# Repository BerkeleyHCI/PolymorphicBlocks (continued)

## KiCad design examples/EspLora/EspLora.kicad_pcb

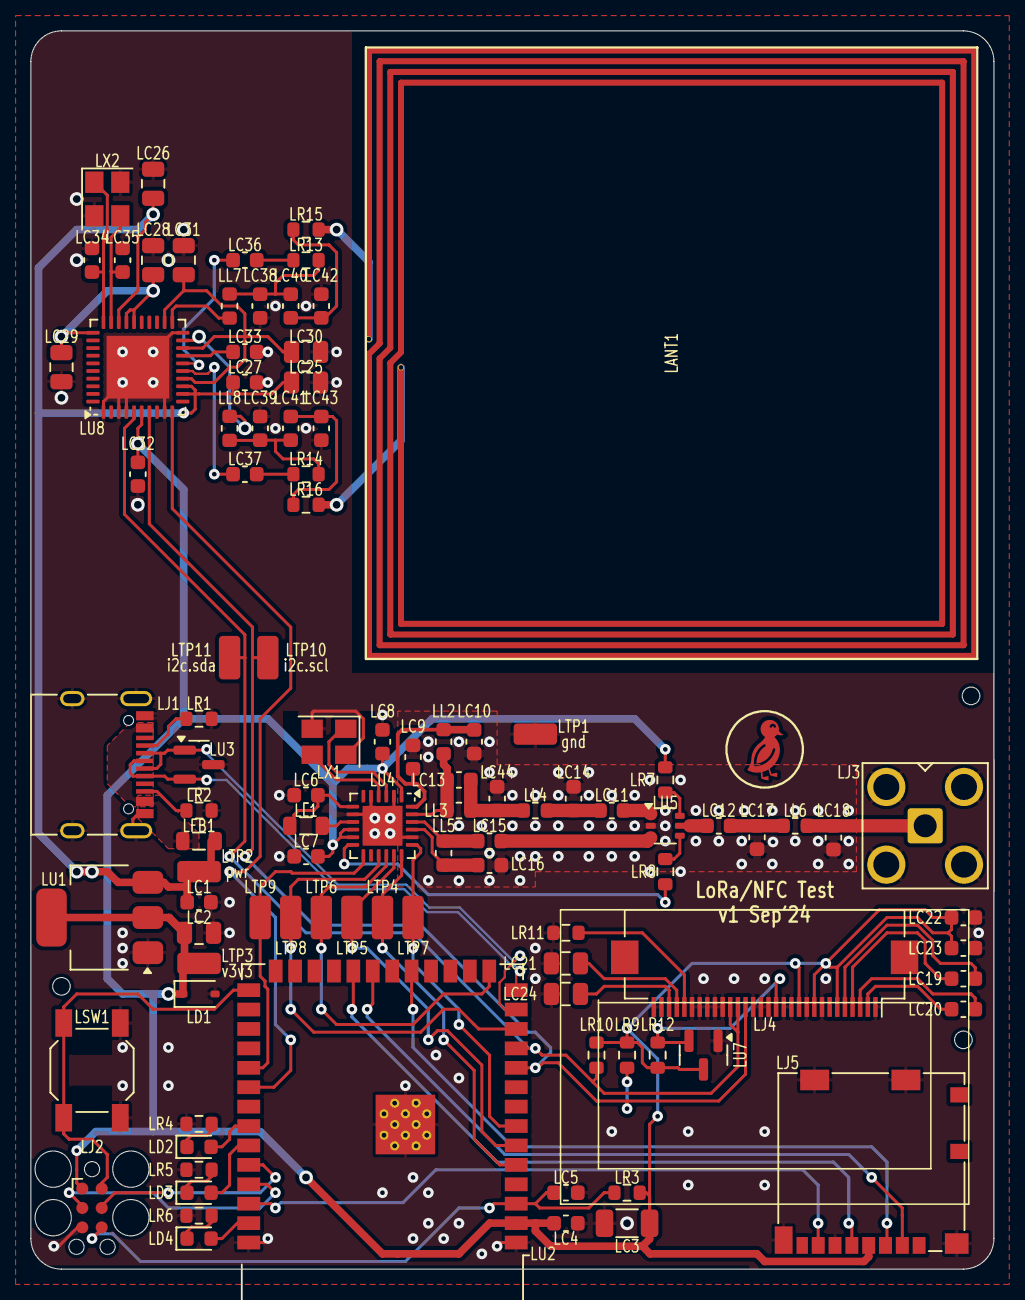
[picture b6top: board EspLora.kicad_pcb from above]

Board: 2 copper layers, 63.0 x 81.0 mm, 105 parts (0 on the bottom side), 74 nets.

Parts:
LANT1: an13219
LC1, LC4, LC7, LC27, LC33: 50V 100nF X7R ±10% 0603 Multilayer Ceramic Capaci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; C_0603_1608Metric
LC2, LC21, LC25, LC26: 25V 4.7uF X5R ±10% 0805 Multilayer Ceramic Capaci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; C_0805_2012Metric
LC3: 25V 22uF X5R ±10% 1206 Multilayer Ceramic Capacit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; C_1206_3216Metric
LC5, LC8, LC19, LC20, LC22, LC23, LC32: 50V 1uF X5R ±10% 0603 Multilayer Ceramic Capacito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; C_0603_1608Metric
LC6: 25V 470nF X7R ±10% 0603 Multilayer Ceramic Capaci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; C_0603_1608Metric
LC9, LC11, LC12, LC42, LC43: 50V 47pF C0G ±5% 0603 Multilayer Ceramic Capacito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; C_0603_1608Metric
LC10: 50V 47nF X7R ±10% 0603 Multilayer Ceramic Capacit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; C_0603_1608Metric
LC13: 250V 2.2pF NP0 ±5% 0603 Multilayer Ceramic Capaci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; C_0603_1608Metric
LC14, LC15, LC16, LC17, LC18: 250V 3pF C0G ±5% 0603 Multilayer Ceramic Capacito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; C_0603_1608Metric
LC24: 25V 10uF X5R ±10% 0805 Multilayer Ceramic Capacit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; C_0805_2012Metric
LC28, LC29, LC30, LC31: 50V 2.2uF X5R ±10% 0805 Multilayer Ceramic Capaci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; C_0805_2012Metric
LC34, LC35, LC44: 50V 10pF C0G ±5% 0603 Multilayer Ceramic Capacito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; C_0603_1608Metric
LC36, LC37: 50V 1nF X7R ±10% 0603 Multilayer Ceramic Capacito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; C_0603_1608Metric
LC38, LC39: 50V 560pF X7R ±10% 0603 Multilayer Ceramic Capaci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; C_0603_1608Metric
LC40, LC41: 50V 150pF X7R ±10% 0603 Multilayer Ceramic Capaci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; C_0603_1608Metric
LD1: 3.6V~3.8V 200mW 3.6V SOD-323 Zener Diodes ROHS; D_SOD-323
LD2: -40?~+85? Red 0603 LED Indication - Discrete ROHS; LED_0603_1608Metric
LD3: 20mA Colorless transparent lens -40?~+85? 585.5nm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; LED_0603_1608Metric
LD4: White 0603 LED Indication - Discrete ROHS; LED_0603_1608Metric
LFB1: ±25% 100?@100MHz 0805 Ferrite Beads ROHS; L_0805_2012Metric
LH1, LH2, LH3: JlcToolingHole_1.152mm
LJ1: COM-15111; USB_C_Receptacle_XKB_U262-16XN-4BVC11
LJ2: Tag-Connect_TC2030-IDC-FP_2x03_P1.27mm_Vertical
LJ3: 901-143; SMA_Amphenol_901-143_Horizontal
LJ4: AFC01-S30FCA-00; Hirose_FH12-30S-0.5SH_1x30-1MP_P0.50mm_Horizontal
LJ5: 104031-0811; microSD_HC_Molex_104031-0811
LL1: 100mA 15uH ±20% 650m? 0805 Inductors (SMD) ROHS; L_0805_2012Metric
LL2: 200mA 47nH ±5% 1? 0603 Inductors (SMD) ROHS; L_0603_1608Metric
LL3: 700mA 3.3nH ±5% 0603 Power Inductors ROHS; L_0603_1608Metric
LL4, LL6: 500mA 8.2nH ±5% 350m? 0603 Inductors (SMD) ROHS; L_0603_1608Metric
LL5: 300mA 12nH ±5% 450m? 0603 Inductors (SMD) ROHS; L_0603_1608Metric
LL7, LL8: 900mA 220nH ±5% 200m? 0603 Inductors (SMD) ROHS; L_0603_1608Metric
LR1, LR2: 100mW Thick Film Resistors 75V ±100ppm/? ±1% 5.1k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; R_0603_1608Metric
LR3, LR12: 100mW Thick Film Resistors 75V ±100ppm/? ±1% 10k?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; R_0603_1608Metric
LR4, LR5, LR6: 100mW Thick Film Resistors 75V ±100ppm/? ±1% 820?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; R_0603_1608Metric
LR7, LR8: 100mW Thick Film Resistors 75V ±100ppm/? ±1% 1k? 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; R_0603_1608Metric
LR9, LR10: 100mW Thick Film Resistors 75V ±100ppm/? ±1% 4.7k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; R_0603_1608Metric
LR11: 100mW Thick Film Resistors 75V ±100ppm/? ±1% 470k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; R_0603_1608Metric
LR13, LR14: 100mW Thick Film Resistors 75V ±100ppm/? ±1% 2.2k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; R_0603_1608Metric
LR15, LR16: 100mW Thick Film Resistors 75V ±1% ±200ppm/? 2.49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; R_0603_1608Metric
LSW1: 5.1mm switch; SW_SPST_SKQG_WithoutStem
LTP1: gnd; TestPoint_TE_RCT_0805
LTP2: pwr; TestPoint_TE_RCT_0805
LTP3: v3v3; TestPoint_TE_RCT_0805
LTP4: lr.sck; TestPoint_TE_RCT_0805
LTP5: lr.mosi; TestPoint_TE_RCT_0805
LTP6: lr.miso; TestPoint_TE_RCT_0805
LTP7: lr_cs; TestPoint_TE_RCT_0805
LTP8: lr_rs; TestPoint_TE_RCT_0805
LTP9: lr_di; TestPoint_TE_RCT_0805
LTP10: i2c.scl; TestPoint_TE_RCT_0805
LTP11: i2c.sda; TestPoint_TE_RCT_0805
LU1: LDL1117S33R; SOT-223-3_TabPin2
LU2: ESP32-S3-WROOM-1-N16R8; ESP32-S3-WROOM-1
LU3: PESD5V0X1BT; SOT-23
LU4: SX1262IMLTRT; QFN-24-1EP_4x4mm_P0.5mm_EP2.6x2.6mm
LU5: PE4259; SOT-363_SC-70-6
LU6: ER-OLED-0.96-1.1; Lcd_Er_Oled0.96_1.1_Outline
LU7: APX803S-29SA-7; SOT-23
LU8: PN7160A1HN/C100Y; HVQFN-40-1EP_6x6mm_P0.5mm_EP4.1x4.1mm
LX1: 30MHz SMD Crystal Resonator 20pF ±10ppm ±30ppm -4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; Crystal_SMD_3225-4Pin_3.2x2.5mm
LX2: 27.12MHz SMD Crystal Resonator 10pF ±10ppm ±30ppm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; Crystal_SMD_3225-4Pin_3.2x2.5mm
svg2mod: G***; Symbol_DucklingSolid

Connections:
Lgnd: LC1.2, LC2.2, LC3.2, LC4.2, LC5.2, LC6.2, LC7.2, LC8.2, LC9.2, LC10.2, LC14.2, LC16.2, LC17.2, LC18.2, LC21.2, LC22.2, LC23.2, LC24.2, LC25.2, LC26.2, LC27.2, LC28.2, LC29.2, LC30.2, LC31.2, LC32.2, LC33.2, LC34.2, LC35.2, LC38.2, LC39.2, LC42.2, LC43.2, LC44.2, LD1.2, LJ1.A1, LJ1.A12, LJ1.B1, LJ1.B12, LJ1.S1, LJ2.5, LJ3.2, LJ4.1, LJ4.8, LJ4.10, LJ4.12, LJ4.13, LJ4.15, LJ4.16, LJ4.17, LJ4.21, LJ4.22, LJ4.23, LJ4.24, LJ4.25, LJ4.29, LJ4.30, LJ5.6, LJ5.11, LR1.1, LR2.1, LR4.2, LR5.2, LR6.2, LR11.2, LSW1.2, LTP1.1, LU1.1, LU2.1, LU2.40, LU2.41, LU3.3, LU4.2, LU4.5, LU4.8, LU4.20, LU4.25, LU5.2, LU7.1, LU8.1, LU8.3, LU8.4, LU8.9, LU8.20, LU8.41, LX1.2, LX1.4, LX2.2, LX2.4
Li2c_pull.i2c.scl: LJ4.18, LR9.2, LTP10.1, LU2.10, LU8.7
Li2c_pull.i2c.sda: LJ4.19, LJ4.20, LR10.2, LTP11.1, LU2.11, LU8.5
Lledb.res.a: LD4.1, LR6.1
Lledb.signal: LD4.2, LU2.39
Lledg.res.a: LD3.1, LR5.1
Lledg.signal: LD3.2, LU2.35
Lledr.res.a: LD2.1, LR4.1
Lledr.signal: LD2.2, LU2.34
Llora.ant_pi.output: LC18.1, LJ3.1, LL6.2
Llora.balun.input: LC15.1, LU5.3
Llora.balun.rfi_n: LC15.2, LL5.1, LU4.22
Llora.balun.rfi_p: LC16.1, LL5.2, LU4.21
Llora.dcc_l.a: LL1.1, LU4.9
Llora.ic.rfo: LC13.2, LL2.2, LL3.1, LU4.23
Llora.ic.vr_pa: LC9.1, LC10.1, LL2.1, LU4.24
Llora.ic.vreg: LC6.1, LL1.2, LU4.7
Llora.rf_sw.ctrl: LR8.1, LU4.12
Llora.rf_sw.ctrl_res.b: LR8.2, LU5.4
Llora.rf_sw.vdd_res.b: LR7.2, LU5.6
Llora.rfc_dcblock.neg: LC12.2, LU5.5
Llora.rfc_dcblock.pos: LC12.1, LC17.1, LL6.1
Llora.tx_dcblock.pos: LC11.1, LU5.1
Llora.tx_pi.output: LC11.2, LC14.1, LL4.2
Llora.xtal.crystal.xtal_in: LU4.3, LX1.1
Llora.xtal.crystal.xtal_out: LU4.4, LX1.3
Lmcu.program_boot_node: LJ2.2, LSW1.1, LU2.27
Lmcu.program_en_node: LC5.1, LJ2.6, LR3.2, LU2.3
Lmcu.program_uart_node.a_tx: LJ2.3, LU2.37
Lmcu.program_uart_node.b_tx: LJ2.4, LU2.36
Lnfc.damp.ant1: LANT1.1, LR15.2
Lnfc.damp.ant2: LANT1.2, LR16.2
Lnfc.emc.out1: LC38.1, LC40.1, LL7.2, LR13.1
Lnfc.emc.out2: LC39.1, LC41.1, LL8.2, LR14.1
Lnfc.ic.rxn: LC37.2, LU8.15
Lnfc.ic.rxp: LC36.2, LU8.16
Lnfc.ic.tx1: LL7.1, LU8.21
Lnfc.ic.tx2: LL8.1, LU8.19
Lnfc.ic.vdd: LC28.1, LC29.1, LU8.26, LU8.27, LU8.31
Lnfc.ic.vddmid: LC33.1, LU8.17
Lnfc.ic.vddtx: LC30.1, LC31.1, LU8.14, LU8.18, LU8.22
Lnfc.ic.xtal.xtal_in: LC34.1, LU8.30, LX2.1
Lnfc.ic.xtal.xtal_out: LC35.1, LU8.29, LX2.3
Lnfc.match.out1: LC40.2, LC42.1, LR15.1
Lnfc.match.out2: LC41.2, LC43.1, LR16.1
Lnfc.reset: LU2.32, LU8.10
Lnfc.rx.rrx1.b: LC36.1, LR13.2
Lnfc.rx.rrx2.b: LC37.1, LR14.2
Loled.c1_cap.neg: LC19.2, LJ4.5
Loled.c1_cap.pos: LC19.1, LJ4.4
Loled.c2_cap.neg: LC20.2, LJ4.3
Loled.c2_cap.pos: LC20.1, LJ4.2
Loled.device.vcc: LC24.1, LJ4.28
Loled.device.vcomh: LC21.1, LJ4.27
Loled.iref_res.a: LJ4.26, LR11.1
Loled_rst.nreset: LJ4.14, LR12.2, LU7.2
Lpwr: LC1.1, LC25.1, LC26.1, LC27.1, LFB1.2, LTP2.1, LU1.3, LU8.12, LU8.13, LU8.28
Lsd.cs: LJ5.2, LU2.21
Lsd.spi.miso: LJ5.7, LU2.38
Lsd.spi.mosi: LJ5.3, LU2.19
Lsd.spi.sck: LJ5.5, LU2.22
Ltp_lora_cs.io: LTP7.1, LU2.7, LU4.19
Ltp_lora_dio.io: LTP9.1, LU2.31, LU4.13
Ltp_lora_rst.io: LTP8.1, LU2.12, LU4.15
Ltp_lora_spi.io.miso: LTP6.1, LU2.15, LU4.16
Ltp_lora_spi.io.mosi: LTP5.1, LU2.6, LU4.17
Ltp_lora_spi.io.sck: LTP4.1, LU2.5, LU4.18
Ltx_cpack.pos.0: LC13.1, LC44.1, LL3.2, LL4.1
Lusb.conn.cc.cc1: LJ1.A5, LR1.2
Lusb.conn.cc.cc2: LJ1.B5, LR2.2
Lusb.pwr: LFB1.1, LJ1.A4, LJ1.A9, LJ1.B4, LJ1.B9
Lusb_chain_0.d_N: LJ1.A7, LJ1.B7, LU2.13, LU3.1
Lusb_chain_0.d_P: LJ1.A6, LJ1.B6, LU2.14, LU3.2
Lv3v3: LC2.1, LC3.1, LC4.1, LC7.1, LC8.1, LC22.1, LC23.1, LC32.1, LD1.1, LJ2.1, LJ4.6, LJ4.9, LJ4.11, LJ5.4, LR3.1, LR7.1, LR9.1, LR10.1, LR12.1, LTP3.1, LU1.2, LU2.2, LU4.1, LU4.10, LU4.11, LU7.3, LU8.6

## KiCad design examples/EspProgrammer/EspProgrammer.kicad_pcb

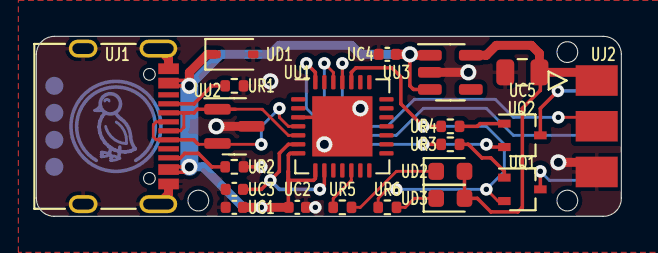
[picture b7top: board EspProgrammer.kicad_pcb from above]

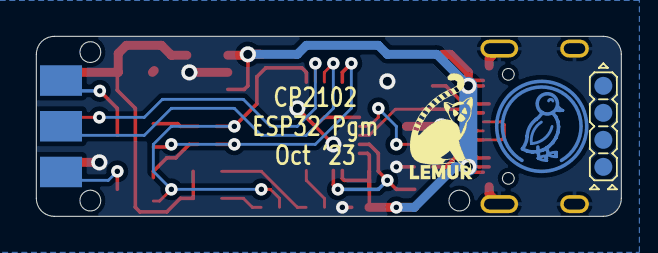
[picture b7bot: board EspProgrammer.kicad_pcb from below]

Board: 2 copper layers, 32.5 x 10.0 mm, 27 parts (3 on the bottom side), 19 nets.

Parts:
UC1, UC2, UC3, UC4: C_0402_1005Metric
UC5: C_0805_2012Metric
UD1: BZT52-B5V6S_R1_00001 (PANJIT International) - 100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; D_SOD-323
UD2: C2290 (Hubei KENTO Elec) - White 0603 Light Emitt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; LED_0603_1608Metric
UD3: KT-0603R (Hubei KENTO Elec) - Red 615~630nm 1.9~2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; LED_0603_1608Metric
UH1, UH2, UH3: JlcToolingHole_1.152mm
UJ1: COM-15111 (Sparkfun); USB_C_Receptacle_XKB_U262-16XN-4BVC11
UJ2: PinHeader2.54 Shrouded 2x3 (Generic); PinHeader_2x03_P2.54mm_EdgeInline
UQ1, UQ2: BC846BW 1B (CBI) - 65V 330mW 100mA 290@2mA,5V 250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; SOT-323_SC-70
UR1, UR2, UR3, UR4, UR5, UR6: R_0402_1005Metric
UU1: CP2102 (Silicon Labs); QFN-28-1EP_5x5mm_P0.5mm_EP3.35x3.35mm
UU2: PESD5V0X1BT (Nexperia); SOT-23
UU3: AP2204K-3.3 (Diodes Incorporated); SOT-23-5
UU4: Duck; Symbol_Duckling
UU5: Lemur; Symbol_LemurSmall
UU6: IdDots4; Indicator_IdDots_4

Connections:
Uauto.boot: UJ2.2, UQ2.3
Uauto.dtr_res.b: UQ1.1, UR3.2
Uauto.en: UJ2.6, UQ1.3
Uauto.rts_res.b: UQ2.1, UR4.2
Ugnd: UC1.2, UC2.2, UC3.2, UC4.2, UC5.2, UD1.2, UJ1.A1, UJ1.A12, UJ1.B1, UJ1.B12, UJ1.S1, UJ2.5, UR1.1, UR2.1, UU1.3, UU1.29, UU2.3, UU3.2
Uled.res.a: UD2.1, UR5.1
Uled_en.res.a: UD3.1, UR6.1
Uusb_chain_0.d_N: UJ1.A7, UJ1.B7, UU1.5, UU2.1
Uusb_chain_0.d_P: UJ1.A6, UJ1.B6, UU1.4, UU2.2
Uusb_uart.conn.A5: UJ1.A5, UR1.2
Uusb_uart.conn.B5: UJ1.B5, UR2.2
Uusbconv.dtr: UQ2.2, UR3.1, UU1.28
Uusbconv.ic.vdd: UC3.1, UU1.6, UU1.9
Uusbconv.rts: UQ1.2, UR4.1, UR6.2, UU1.24
Uusbconv.suspend: UR5.2, UU1.12
Uusbconv.uart.rx: UJ2.3, UU1.25
Uusbconv.uart.tx: UJ2.4, UU1.26
Uv3v3: UC5.1, UD2.2, UD3.2, UJ2.1, UU3.5
Uvusb: UC1.1, UC2.1, UC4.1, UD1.1, UJ1.A4, UJ1.A9, UJ1.B4, UJ1.B9, UU1.7, UU1.8, UU3.1, UU3.3

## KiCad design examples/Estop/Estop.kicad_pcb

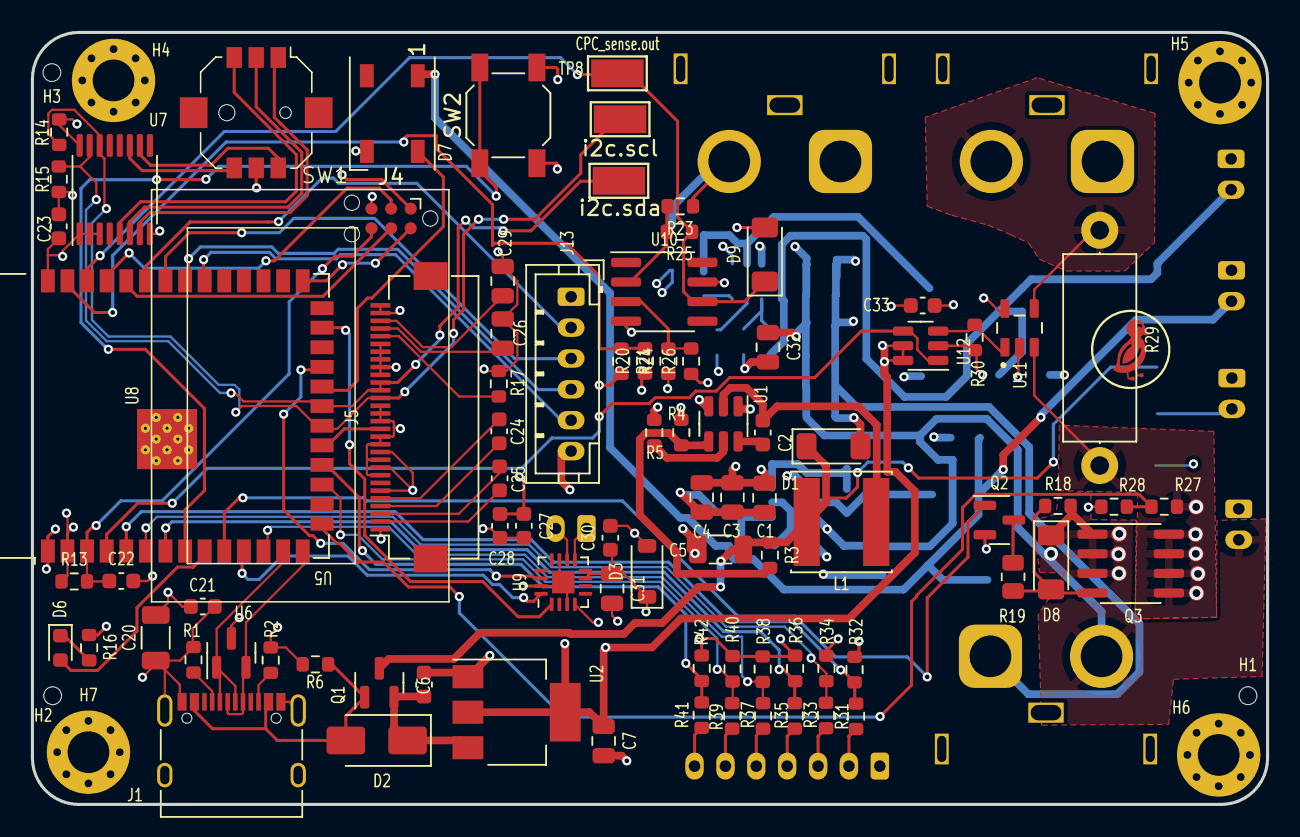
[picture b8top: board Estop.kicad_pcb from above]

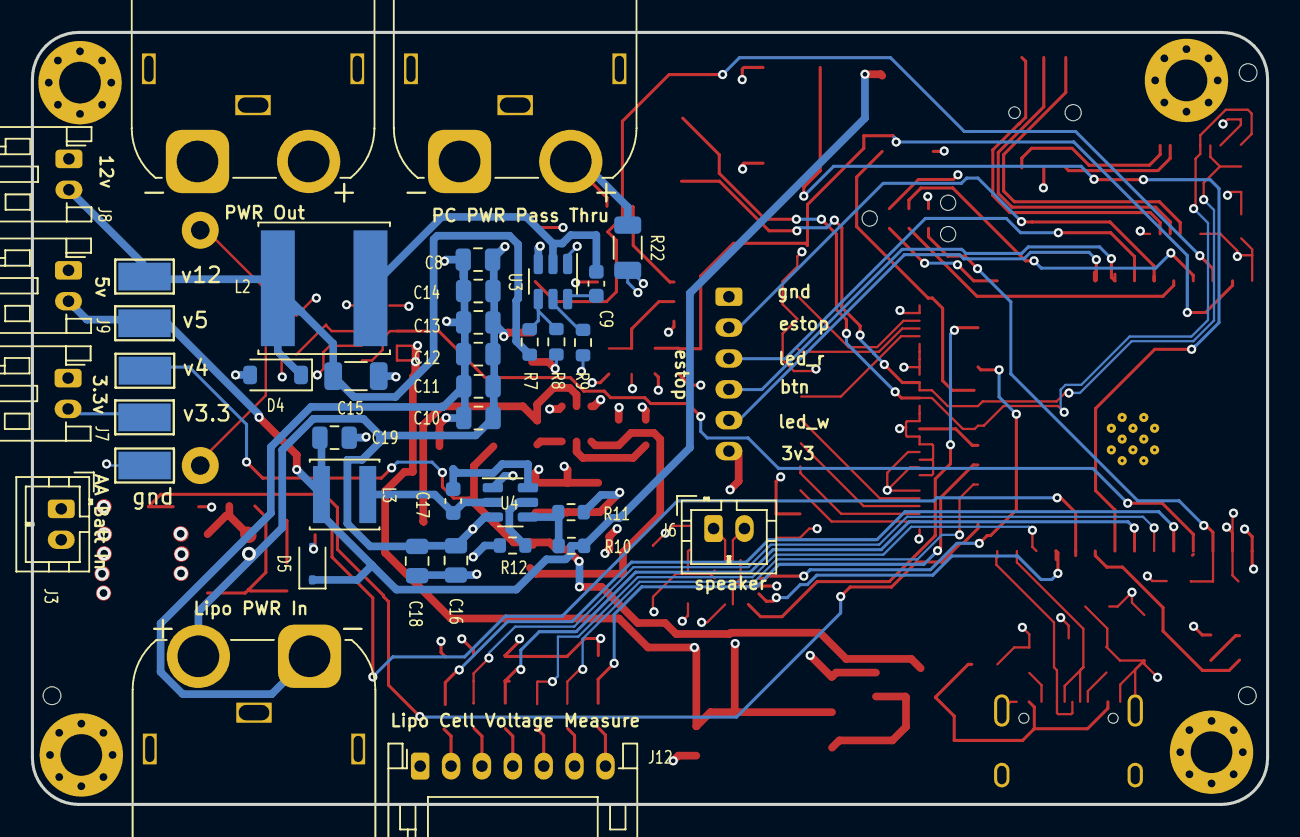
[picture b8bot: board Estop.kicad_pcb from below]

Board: 4 copper layers, 80.0 x 50.0 mm, 133 parts (39 on the bottom side), 81 nets.

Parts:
C1, C3, C4, C7, C8, C10, C11, C12, C13, C14, C16, C18, C19, C26, C29, C31, C32: C_0805_2012Metric
C2, C6, C9, C17, C21, C22, C23, C24, C25, C27, C28, C30, C33: C_0603_1608Metric
C5, C15, C20: C_1206_3216Metric
D1, D9: D_MiniMELF
D2: 100V 850mV@2A 2A SMA(DO-214AC) Schottky Barrier D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; D_SMA
D3: 5?A@1V 90? Single 3.6V~3.8V 350mW 3.4V SOD-123 Ze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; D_SOD-123
D4: 100nA@8V 30? Single 12.74V~13.26V 500mW 13V SOD-1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; D_SOD-123
D5: 1?A@2V 40? Single 5.6V~5.71V 200mW 5.6V SOD-323 Z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; D_SOD-323
D6: Red 615~630nm 1.9~2.2V 0603 Light Emitting Diodes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; LED_0603_1608Metric
D7: WS2812B; LED_WS2812B_PLCC4_5.0x5.0mm_P3.2mm
D8: 2?A@5V 7? 7V~7.9V 500mW 7.5V LL-34 Zener Diodes R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; D_MiniMELF
H1, H2, H3: JlcToolingHole_1.152mm
H4, H5, H6, H7: M2.5; MountingHole_2.7mm_M2.5_Pad_Via
J1: COM-15111; USB_C_Receptacle_XKB_U262-16XN-4BVC11
J2: B2B-PH-K; AMASS_XT60IPW-M_1x03_P7.20mm_Horizontal
J3, J6: B2B-PH-K; JST_PH_B2B-PH-K_1x02_P2.00mm_Vertical
J4: Tag-Connect_TC2030-IDC-NL_2x03_P1.27mm_Vertical
J5: AFC01-S30FCA-00; Hirose_FH12-30S-0.5SH_1x30-1MP_P0.50mm_Horizontal
J7, J8, J9: S2B-PH-K; JST_PH_S2B-PH-K_1x02_P2.00mm_Horizontal
J10, J11: S2B-PH-K; AMASS_XT60IPW-M_1x03_P7.20mm_Horizontal
J12: S7B-PH-K; JST_PH_S7B-PH-K_1x07_P2.00mm_Horizontal
J13: B6B-PH-K; JST_PH_B6B-PH-K_1x06_P2.00mm_Vertical
L1: L_Sunlord_SWPA6045S
L2: L_Sunlord_SWPA8040S
L3: L_Sunlord_SWPA4030S
Q1: 30V 4A 44m?@10V,4.3A 1.4W 1.3V@250?A P Channel SO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; SOT-23
Q2: 60V 115mA 200mW 7.5?@10V,500mA 2.5V@250?A N Chann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; SOT-23
Q3: 30V 29A 7.8W 5m?@10V,15A 2.5V@250?A P Channel SOI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; SOIC-8_3.9x4.9mm_P1.27mm
R1, R2, R3, R4, R5, R6, R7, R8, R9, R10, R11, R12, R13, R14, R15, R16, R17, R18, R20, R21, R23, R24, R25, R26, R27, R28, R30, R31, R32, R33, R34, R35, R36, R37, R38, R39, R40, R41, R42: R_0603_1608Metric
R19: R_0805_2012Metric
R22: R_1206_3216Metric
R29: 4.7m, 1%, 2.0 W; R_Axial_DIN0414_L11.9mm_D4.5mm_P15.24mm_Horizontal
SW1: SKRHABE010; DirectionSwitch_Alps_SKRH
SW2: 5.1mm switch; SW_SPST_SKQG_WithoutStem
TP1: gnd; TestPoint_Keystone_5015_Micro-Minature
TP2: _reg_4v_pwr_out_link; TestPoint_Keystone_5015_Micro-Minature
TP3: v3v3; TestPoint_Keystone_5015_Micro-Minature
TP4: v12; TestPoint_Keystone_5015_Micro-Minature
TP5: v5; TestPoint_Keystone_5015_Micro-Minature
TP6: i2c.scl; TestPoint_Keystone_5015_Micro-Minature
TP7: i2c.sda; TestPoint_Keystone_5015_Micro-Minature
TP8: _cPc_sense_out_link; TestPoint_Keystone_5015_Micro-Minature
U1, U3, U4: TPS54202H; SOT-23-6
U2: LDL1117S33R; SOT-223-3_TabPin2
U5: ESP32-S3-WROOM-1-N16R8; ESP32-S3-WROOM-1
U6: PESD5V0X1BT; SOT-23
U7: PCA9554APW,118; TSSOP-16_4.4x5mm_P0.65mm
U8: ER-OLED-0.96-1.1; Lcd_Er_Oled0.96_1.1_Outline
U9: MAX98357AETE+T; QFN-16-1EP_3x3mm_P0.5mm_EP1.45x1.45mm
U10: OPA197IDR; SOIC-8_3.9x4.9mm_P1.27mm
U11: INA139NA/3K; SOT95P280X145-5N
U12: TLV9061S; SOT-23-6
svg2mod: G***; Symbol_DucklingSolid

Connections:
(adapter)jst_estop.pins.2.src: J13.2, U5.35
(adapter)jst_estop.pins.3.src: J13.3, U5.34
(adapter)jst_estop.pins.4.src: J13.4, U5.33
(adapter)jst_estop.pins.5.src: J13.5, U5.32
(adapter)jst_out.pins.2.src: J11.2, R29.2, U11.4
(adapter)lipo_pins.pins.2.src: J12.2, R31.1
(adapter)lipo_pins.pins.3.src: J12.3, R33.1
(adapter)lipo_pins.pins.4.src: J12.4, R35.1
(adapter)lipo_pins.pins.5.src: J12.5, R37.1
(adapter)lipo_pins.pins.6.src: J12.6, R39.1
(adapter)lipo_pins.pins.7.src: J12.7, R41.1
(adapter)vbatt_pin.pins.2.src: J10.2, R22.2, R23.1
cPc_sense.amp.r1.b: R23.2, R25.2, U10.2
cPc_sense.amp.r2.b: R24.2, R26.2, U10.3
cPc_sense.out: D9.1, R25.1, TP8.1, U5.38, U10.6
cbatt_sense.ic.vout: R30.1, U11.1, U12.3
cbatt_sense.out: U5.4, U12.1, U12.4
dir.a: SW1.1, U7.7
dir.b: SW1.4, U7.10
dir.c: SW1.3, U7.5
dir.center: SW1.2, U7.6
dir.d: SW1.6, U7.11
gnd: C1.2, C3.2, C4.2, C5.2, C6.2, C7.2, C8.2, C10.2, C11.2, C12.2, C13.2, C14.2, C15.2, C16.2, C18.2, C19.2, C20.2, C21.2, C22.2, C23.2, C26.2, C27.2, C28.2, C29.2, C30.2, C31.2, C32.2, C33.2, D1.2, D3.2, D4.2, D5.2, D7.3, D9.2, J1.A1, J1.A12, J1.B1, J1.B12, J1.S1, J2.1, J4.5, J5.1, J5.8, J5.10, J5.12, J5.13, J5.15, J5.16, J5.17, J5.21, J5.22, J5.23, J5.24, J5.25, J5.29, J5.30, J7.1, J8.1, J9.1, J10.1, J11.1, J12.1, J13.1, Q2.2, R1.1, R2.1, R4.2, R6.2, R8.2, R11.2, R16.2, R17.2, R21.2, R26.1, R28.2, R30.2, R32.2, R34.2, R36.2, R38.2, R40.2, R42.2, SW1.5, SW2.2, TP1.1, U1.1, U2.1, U3.1, U4.1, U5.1, U5.40, U5.41, U6.3, U7.1, U7.2, U7.3, U7.8, U9.3, U9.11, U9.15, U9.17, U10.4, U11.2, U12.2
i2c_chain_0.scl: J5.18, R14.2, TP6.1, U5.20, U7.14
i2c_chain_0.sda: J5.19, J5.20, R15.2, TP7.1, U5.21, U7.15
led.res.a: D6.1, R16.1
led.signal: D6.2, U5.9
mcu.program_boot_node: J4.2, U5.27
mcu.program_en_node: C22.1, J4.6, R13.2, U5.3
mcu.program_uart_node.a_tx: J4.3, U5.37
mcu.program_uart_node.b_tx: J4.4, U5.36
mosfet.control: Q2.1, U5.10
mosfet.output: Q3.5, Q3.6, Q3.7, Q3.8, R27.1, R29.1, U11.3
mosfet.pre.drain: Q2.3, R19.2
mosfet.pull.b: D8.2, Q3.4, R18.2, R19.1
npx.din: D7.4, U5.22
oled.c1_cap.neg: C24.2, J5.5
oled.c1_cap.pos: C24.1, J5.4
oled.c2_cap.neg: C25.2, J5.3
oled.c2_cap.pos: C25.1, J5.2
oled.device.vcc: C29.1, J5.28
oled.device.vcomh: C26.1, J5.27
oled.iref_res.a: J5.26, R17.1
oled.reset: J5.14, U5.19
pwr: C6.1, D2.1, Q1.2, U2.3
reg_4v.boot_cap.neg: C2.2, L1.1, U1.2
reg_4v.boot_cap.pos: C2.1, U1.6
reg_4v.en_res.b: R5.2, U1.5
reg_4v.fb.output: R3.2, R4.1, U1.4
reg_4v.pwr_out: C5.1, D1.1, L1.2, Q1.3, R3.1, TP2.1
reg_5v.boot_cap.neg: C17.2, L3.1, U4.2
reg_5v.boot_cap.pos: C17.1, U4.6
reg_5v.en_res.b: R12.2, U4.5
reg_5v.fb.output: R10.2, R11.1, U4.4
reg_12v.boot_cap.neg: C9.2, L2.1, U3.2
reg_12v.boot_cap.pos: C9.1, U3.6
reg_12v.en_res.b: R9.2, U3.5
reg_12v.fb.output: R7.2, R8.1, U3.4
spk_drv.i2s.sck: U5.11, U9.16
spk_drv.i2s.sd: U5.25, U9.1
spk_drv.i2s.ws: U5.23, U9.14
spk_drv.out.a: J6.1, U9.9
spk_drv.out.b: J6.2, U9.10
switch.out: SW2.1, U5.8
usb.conn.A5: J1.A5, R1.2
usb.conn.B5: J1.B5, R2.2
usb_chain_0.d_N: J1.A7, J1.B7, U5.13, U6.1
usb_chain_0.d_P: J1.A6, J1.B6, U5.14, U6.2
v3v3: C7.1, C20.1, C21.1, C23.1, C27.1, C28.1, C30.1, C31.1, C33.1, D3.1, J4.1, J5.6, J5.9, J5.11, J7.2, J13.6, R13.1, R14.1, R15.1, TP3.1, U2.2, U5.2, U7.16, U9.4, U9.7, U9.8, U11.5, U12.5, U12.6
v5: C19.1, D5.1, D7.1, J9.2, L3.2, R10.1, TP5.1
v12: C15.1, D4.1, J8.2, L2.2, R7.1, TP4.1
vPc_sense.output: R20.2, R21.1, U5.39
v_sense[0].output: R31.2, R32.1, U5.5
v_sense[1].output: R33.2, R34.1, U5.6
v_sense[2].output: R35.2, R36.1, U5.7
v_sense[3].output: R37.2, R38.1, U5.12
v_sense[4].output: R39.2, R40.1, U5.17
v_sense[5].output: R41.2, R42.1, U5.18
vbatt: C1.1, C3.1, C4.1, C8.1, C10.1, C11.1, C12.1, C13.1, C14.1, C16.1, C18.1, C32.1, D8.1, J2.2, J3.2, Q3.1, Q3.2, Q3.3, R5.1, R9.1, R12.1, R18.1, R20.1, R22.1, R24.1, U1.3, U3.3, U4.3, U10.7
vbatt_sense.output: R27.2, R28.1, U5.15
vusb: D2.2, J1.A4, J1.A9, J1.B4, J1.B9, Q1.1, R6.1
